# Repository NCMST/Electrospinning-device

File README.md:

# Electrosining system

Electrospinning is the process of spinning a filament of material (such as nylon) on a spinning machine. This process is used in the production of fiber products, such as yarn, thread, and netting.

## Device function

- Siringe pump control via stepper motor
- Temperature control via triac
- Humidity control via triac
- Rotari colector control via DC motor driver control via L298N
- UI interface made with Encoder and SSD1306 display
- Communication with ESP32-S3 via UART
- Communication with ESP32-S3 via MQTT

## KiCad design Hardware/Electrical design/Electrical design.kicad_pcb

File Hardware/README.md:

# Electrospinning Device Based on ESP32-S3

## Hardware Architecture & Component Analysis

Key Components Diagram

```mermaid
---
config:
  theme: 'base'
  themeVariables:
    primaryColor: '#BB2528'
    primaryTextColor: '#fff'
    primaryBorderColor: '#7C0000'
    lineColor: '#F8B229'
    secondaryColor: '#006100'
    tertiaryColor: '#fff'
---
classDiagram
    direction TB
    atx24 --> esp32s3 : Power supply (5V/3.3V)
    esp32s3 --> atx24 : PS_ON Control signal
    
    %% Motion
    esp32s3 --> TMC2209 : Siringe pump (UART/Step/Dir)
    esp32s3 --> DRV8833 : DC Collector (PWM Bidirectional)
    
    %% UI & Sensors
    esp32s3 --> SSD1306 : UI Display (I2C)
    Encoder --> esp32s3 : UI Input
    GXHT30 --> esp32s3 : Environment Sensor (I2C)
    Termoresistor --> esp32s3 : Safety sensor (ADC)
    
    %% AC Control
    esp32s3 --> Triac1 : 220V Temp control (Opto-isolated)
    esp32s3 --> Triac2 : 220V Humid control (Opto-isolated)
    
    %% High Voltage
    Voltage2 --> Collector : HV Supply (Isolated)

    atx24 : ATX 350W PSU
    esp32s3 : WeAct ESP32-S3-N16R8
    TMC2209 : Silent Stepper Driver (UART)
    DRV8833 : Dual H-Bridge (High Efficiency)
    GXHT30 : Temp/Hum Sensor
    SSD1306 : 128x64 OLED

```
## Components Details

- Power supply 350W : ATX24 
- Stepper motor driver performance up to 35V and ± 1A, motors in fuji, half, 1/4, 1/8, and 1/16 step modes : A4988 
- Temperature and humidity sensor : GXHT30
- Push button encoder : Encoder
- LCD display : SSD1306
- Thermistor : Termoresistor
- Temperature control BTA24 220V : Triac1
- Humidity control BTA24 220V : Triac2
- DC 2-10V 1.5A motor driver : L298N
- 12V : Voltage
- High voltage power supply : Voltage2

--- 
# Components Details & PIN Compatibility (Fallbacks)
## MCU
### WeAct Studio ESP32-S3

* ESP32-S3-N16R8 (WeAct Studio)
	+ Main: WeAct Studio ESP32-S3 (16MB Flash / 8MB PSRAM)
	+ Fallback 1: ESP32-S3-DevKitC-1 (Full size, compatible pinout for most GPIOs)
	+ Fallback 2: Waveshare ESP32-S3-N8R2 (Same core, check mounting holes)

## Stepper Driver
### TMC2209 (Syringe Pump)

* TMC2209 (Ultra-silent, UART control for current/StallGuard)
	+ Fallback (Pin/Logic Compatible): TMC2208: Same pins, but lacks StallGuard (sensorless homing)
	+ Fallback (Pin/Logic Compatible): TMC2225: Similar performance, different package but often available on same-pinout modules
	+ Note: UART communication is essential for real-time current adjustment to prevent motor overheating

## DC Motor Driver
### DRV8833 (Collector)

* DRV8833 (Dual H-Bridge, MOSFET based)
	+ Why: Replaces L298N because it doesn't need a heatsink and supports low voltage (2V-10V) with high efficiency
	+ Fallback (Logic Compatible): TB6612FNG: Identical logic (IN1, IN2, PWM), very efficient
	+ Fallback (Logic Compatible): MAX1508: For very small DC motors, low heat

[Documentation](https://lastminuteengineers.com/drv8833-arduino-tutorial/)

## Environmental Sensor
### GXHT30

* GXHT30 (I2C)
	+ Fallback (I2C / Software Compatible): SHT30 / SHT31: The industry standard, identical I2C registers
	+ Fallback (I2C / Software Compatible): SHT40: Newer generation, lower power, same I2C bus

## Display
### SSD1306 OLED

* SSD1306 (128x64, I2C)
	+ Fallback (I2C Compatible): SH1106: 1.3" OLED, requires a minor offset change in Zephyr dts
	+ Fallback (I2C Compatible): SSD1309: 2.4" Large OLED for better visibility in the lab

 [Product link](https://aliexpress.ru/item/1005004958941138.html?spm=a2g2w.orderdetail.0.0.6f374aa6PABbVD&sku_id=12000031156235749)

## AC Control
### BTA24 + MOC3041

* BTA24 (25A Triac) + MOC3041 (Zero-cross Opto)
	+ Fallback (Safety Compatible): MOC3063: Higher isolation voltage
	+ Fallback (Safety Compatible): BTA41: If higher current (40A) is needed for heavy heating elements

## PIN Mapping Analysis (ESP32-S3 WeAct)

To ensure the TMC2209 UART and other peripherals don't conflict:

| Peripheral | PIN Function | GPIO | Logic Type |
| --- | --- | --- | --- |  
| I2C Bus | SDA / SCL | 17/18 | Shared (Sensors + Display) |
| TMC2209 | UART TX / RX | 15 / 16 | Serial Config | 
| TMC2209 | STEP / DIR | 41 / 42 | High-speed Pulse | 
| DRV8833 | PWM(IN1) / IN2 | 4, 5 | Motor Speed/Dir | 
| ATX24 | PS_ON | 7 | Power Control | 
| Encoder | A / B / SW | 1, 2, 3 | UI Navigation | 
| Triacs | Trigger 1 / 2 | 39 / 40 | AC Switching | 
| Thermistor | ADC Input | 10 | Analog Temp |

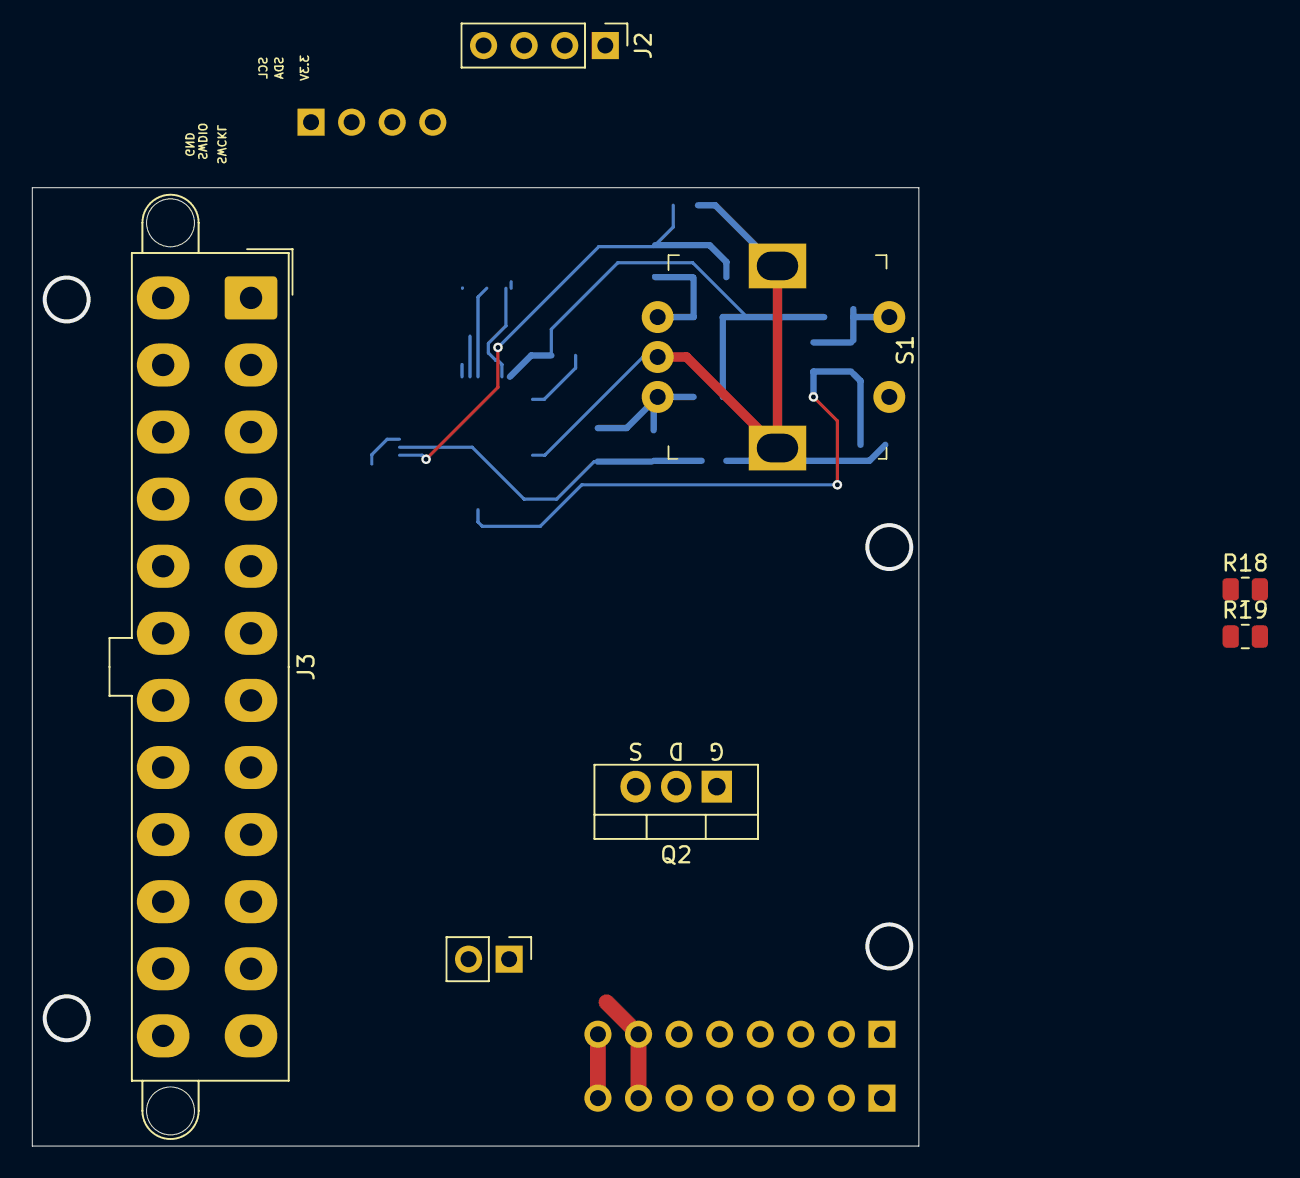
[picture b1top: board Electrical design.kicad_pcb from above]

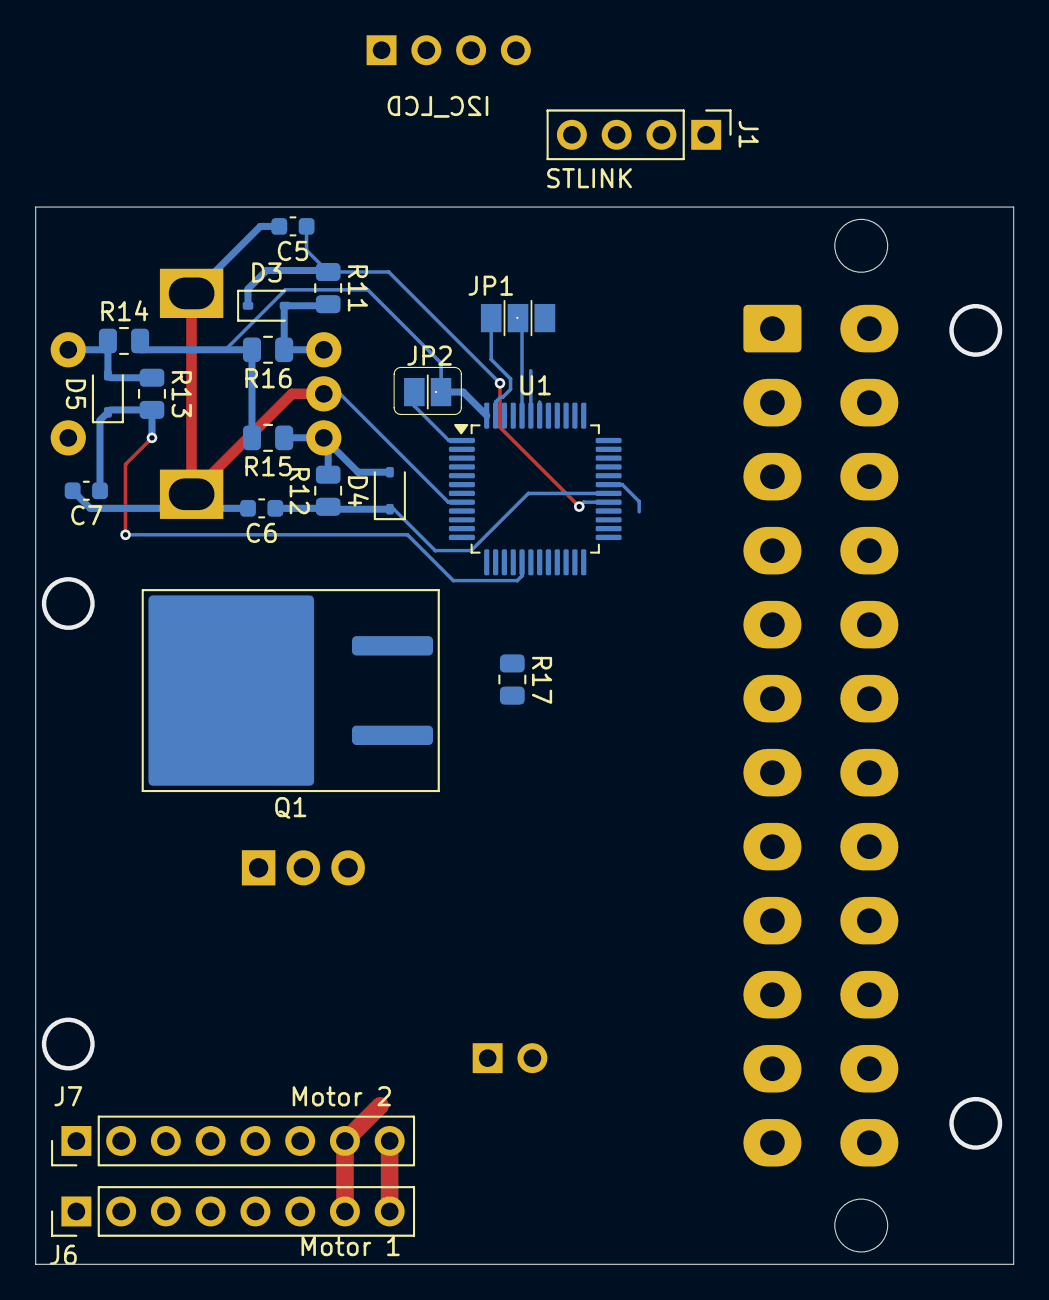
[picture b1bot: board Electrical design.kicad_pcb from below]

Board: 2 copper layers, 55.5 x 60.0 mm, 27 parts (20 on the bottom side), 21 nets.

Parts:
C5, C6, C7: 10nF; C_0603_1608Metric
D3, D4, D5: 1N4148WS; D_SOD-323
J1: STLINK; PinHeader_1x04_P2.54mm_Vertical
J2: LCD; PinHeader_1x04_P2.54mm_Vertical
J3: ATX-24; Molex_Mini-Fit_Jr_5566-24A2_2x12_P4.20mm_Vertical
J5: Transformer; PinHeader_1x02_P2.54mm_Vertical
J6: Motor 1; PinHeader_1x08_P2.54mm_Vertical
J7: Motor 2; PinHeader_1x08_P2.54mm_Vertical
JP1: BOOT; JUMPER_SMD_1x3
JP2: VBAT; JUMPER_SMD_1x2
Q1: FDB13AN06A0; TO-263-2
Q2: IRLZ34N; TO-220-3_Vertical_GDS
R11, R12, R13, R14, R15, R16, R17: 10k; R_0805_2012Metric
R18, R19: 1k; R_0805_2012Metric
S1: PEC11R-4215F-S0024; Rotary_Encoder_Switched_PEC11R
U1: STM32F103C8Tx; LQFP-48_7x7mm_P0.5mm

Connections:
+3.3V: J1.1, J2.2, J3.1 (+3.3V), J3.2 (+3.3V), J3.12 (+3.3V), J3.13 (+3.3V), JP1.3 (B), JP2.2 (B), R14.2, R15.2, R16.2, U1.9 (VDDA), U1.24 (VDD), U1.36 (VDD), U1.48 (VDD)
+5V: J3.4 (+5V), J3.6 (+5V), J3.21 (+5V), J3.22 (+5V), J3.23 (+5V)
+12V: J3.10 (+12V), J3.11 (+12V), J5.1
/Encoder/ENC_A: C5.1, D3.1 (K), R11.1, U1.29 (PA8)
/Encoder/ENC_B: C6.1, D4.1 (K), R12.1, U1.30 (PA9)
/Encoder/ENC_SW: C7.1, D5.1 (K), R13.2, U1.17 (PA7)
/MOSFET_DRIVER/PWM: Q1.1 (G), Q2.1 (G), R17.2, U1.31 (PA10)
/Power/PWR_OK: R18.1, R19.2
/SCL: J2.4, U1.42 (PB6)
/SDA: J2.3, U1.43 (PB7)
/SWCLK: J1.4, U1.37 (PA14)
/SWDIO: J1.3, U1.34 (PA13)
GND: C5.2, C6.2, C7.2, J1.2, J2.1, J3.3 (GND), J3.5 (GND), J3.7 (GND), J3.15 (GND), J3.16 (PS_ON#), J3.17 (GND), J3.18 (GND), J3.19 (GND), J3.24 (GND), J6.7, J7.7, JP1.1 (A), Q1.3 (S), Q2.3 (S), R17.1, R19.1, S1.2, S1.3, S1.C (COM), U1.8 (VSSA), U1.23 (VSS), U1.35 (VSS), U1.47 (VSS)
unnamed: D3.2 (A), R11.2, R16.1, S1.A (CH_A)
unnamed: D4.2 (A), R12.2, R15.1, S1.B (CH_B)
unnamed: D5.2 (A), R13.1, R14.1, S1.1
unnamed: J3.8 (PWR_OK), R18.2
unnamed: JP1.2 (C), U1.44 (BOOT0)
unnamed: JP2.1 (A), U1.1 (VBAT)
unnamed: J5.2, Q1.2 (D), Q2.2 (D)
P,+12: J6.8, J7.8

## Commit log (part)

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2025-02-17 update hardware test
2025-03-02 Add PWM duty option
2025-03-02 Corect link
2025-03-02 Update buils action and info
2025-03-02 Update build file
2025-03-02 Update bulld action
2025-03-02 Update info
2025-03-05 Add 50Hz PWM
2025-03-11 Add freq option
2025-06-03 Update schematic
2026-03-20 new branch
2026-03-20 modified: README.md
2026-03-21 update hw architecture
2026-03-21 update the softwase architecture
2026-03-21 update doc
2026-04-04 refactor: update README.md for improved hardware architecture clarity and component analysis
2026-04-05 update README.md with additional diagrams and documentation links for improved clarity
